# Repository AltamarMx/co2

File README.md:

# co2
Rama de desarrollo, prueba

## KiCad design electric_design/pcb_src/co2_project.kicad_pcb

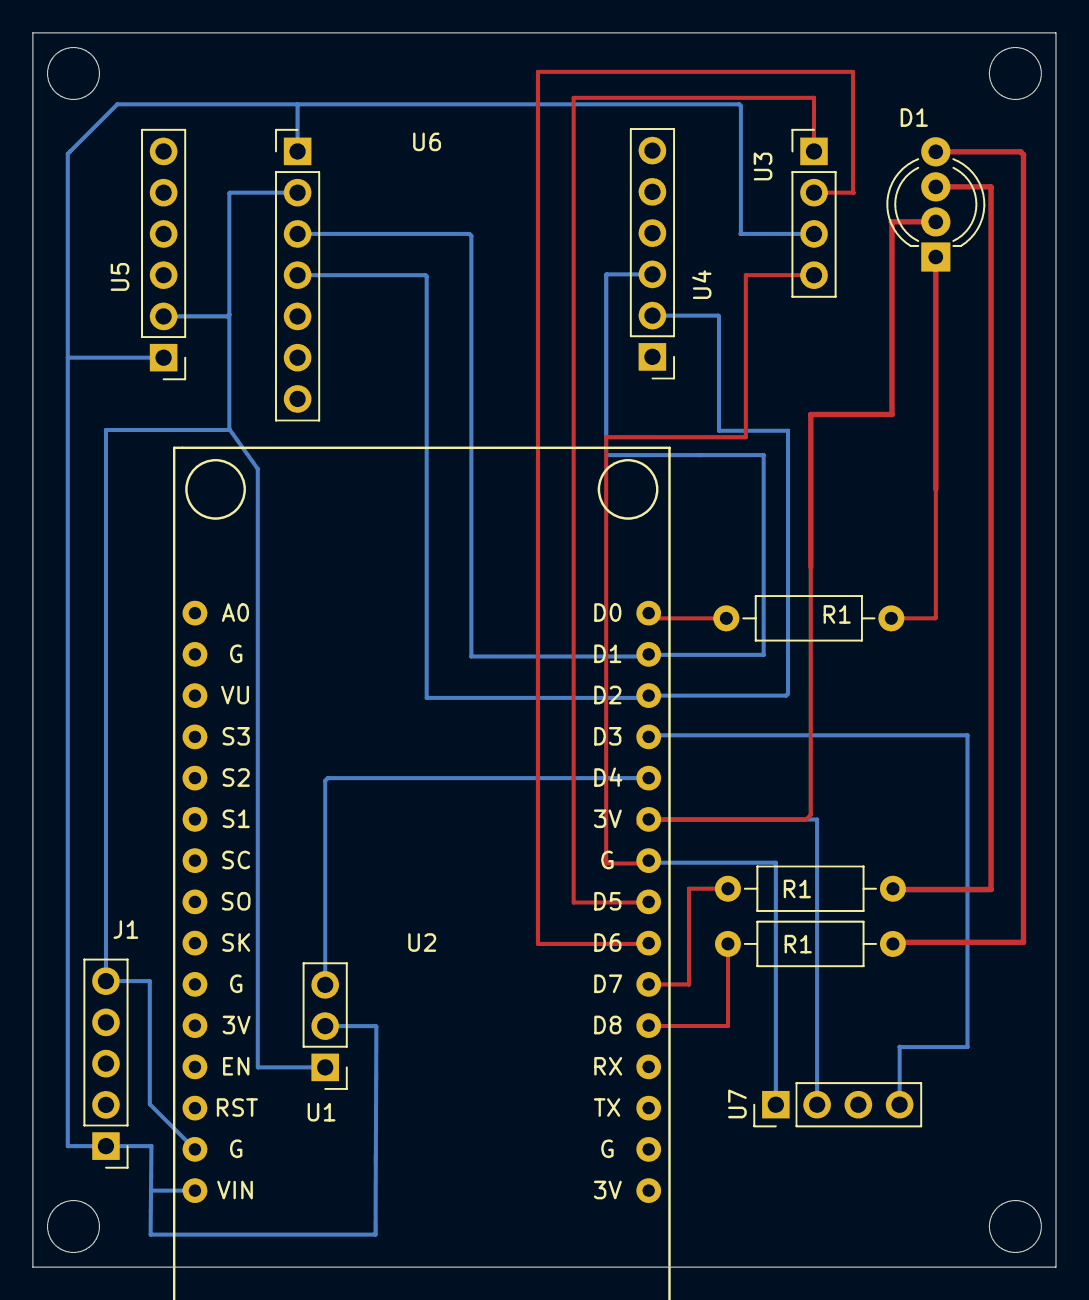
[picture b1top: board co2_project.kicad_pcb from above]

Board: 2 copper layers, 63.0 x 76.0 mm, 12 parts (0 on the bottom side), 16 nets.

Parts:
D1: LED_RGB; LED_D5.0mm-4_RGB_Wide_Pins
J1: 5v; PinHeader_1x05_P2.54mm_Vertical
R1, R1#2, R1#3: 220; R_Axial_DIN0207_L6.3mm_D2.5mm_P10.16mm_Horizontal
U1: Buzzer_activo; PinHeader_1x03_P2.54mm_Vertical
U2: NodeMCU_1.0_(ESP-12E); NodeMCU-LoLinV3
U3: Display; PinHeader_1x04_P2.54mm_Vertical
U4: s8; PinHeader_1x06_P2.54mm_Vertical
U5: lp; PinHeader_1x06_P2.54mm_Vertical
U6: sen0220_scd30; PinHeader_1x07_P2.54mm_Vertical
U7: boton_grove; PinHeader_1x04_P2.54mm_Vertical

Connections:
unnamed: D1.1, R1#3.2
unnamed: D1.2, U2.25, U7.2
unnamed: D1.3, R1#2.2
unnamed: D1.4, R1.2
unnamed: J1.1, U1.2, U2.15, U3.3, U5.1, U6.1
unnamed: J1.5, U1.1, U2.14, U5.2, U6.2
unnamed: R1.1, U2.20
unnamed: R1#2.1, U2.21
unnamed: R1#3.1, U2.30
unnamed: U1.3, U2.26
unnamed: U2.22, U3.2
unnamed: U2.23, U3.1
unnamed: U2.24, U3.4, U7.1
unnamed: U2.27, U7.4
unnamed: U2.28, U4.2, U6.4
unnamed: U2.29, U4.3, U6.3

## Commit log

2021-09-24 rama de desarrollo
2021-10-26 agregue datos fluke de la fecha 18-21/10/2021
2021-10-26 agregue archivos editables de el nuevo diseño PCB
2021-10-26 agregue nuevo esquematico de la nueva version
2021-10-26 agregue vistas 3D del nuevo PCB
2021-10-26 agregue archivos gerber del nuevo diseño PCB
